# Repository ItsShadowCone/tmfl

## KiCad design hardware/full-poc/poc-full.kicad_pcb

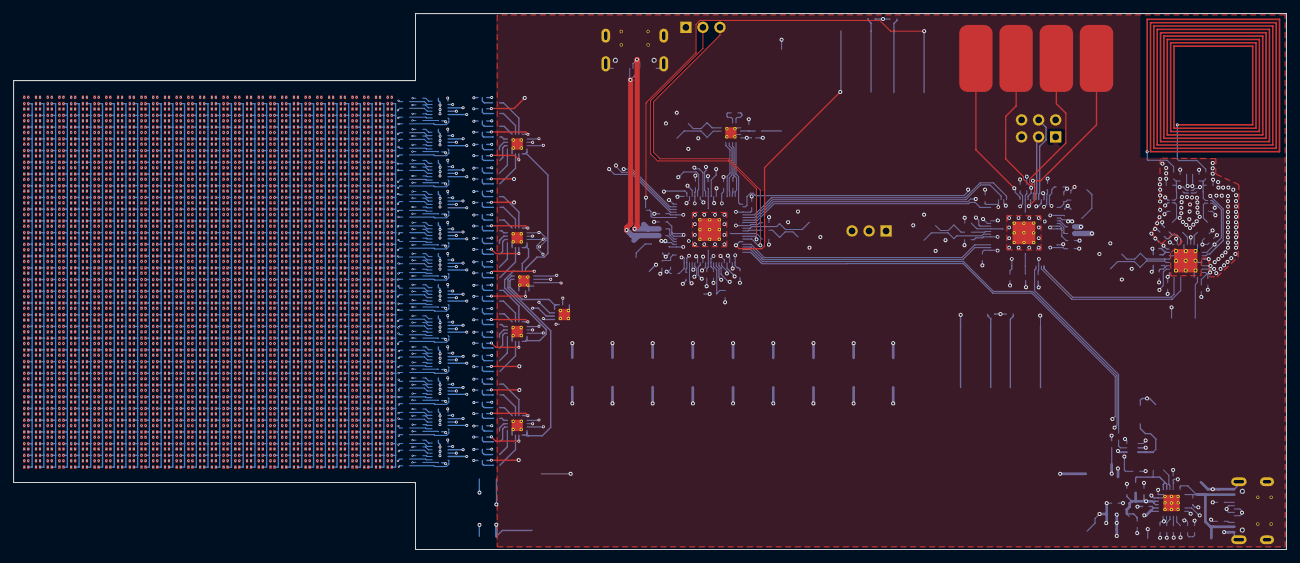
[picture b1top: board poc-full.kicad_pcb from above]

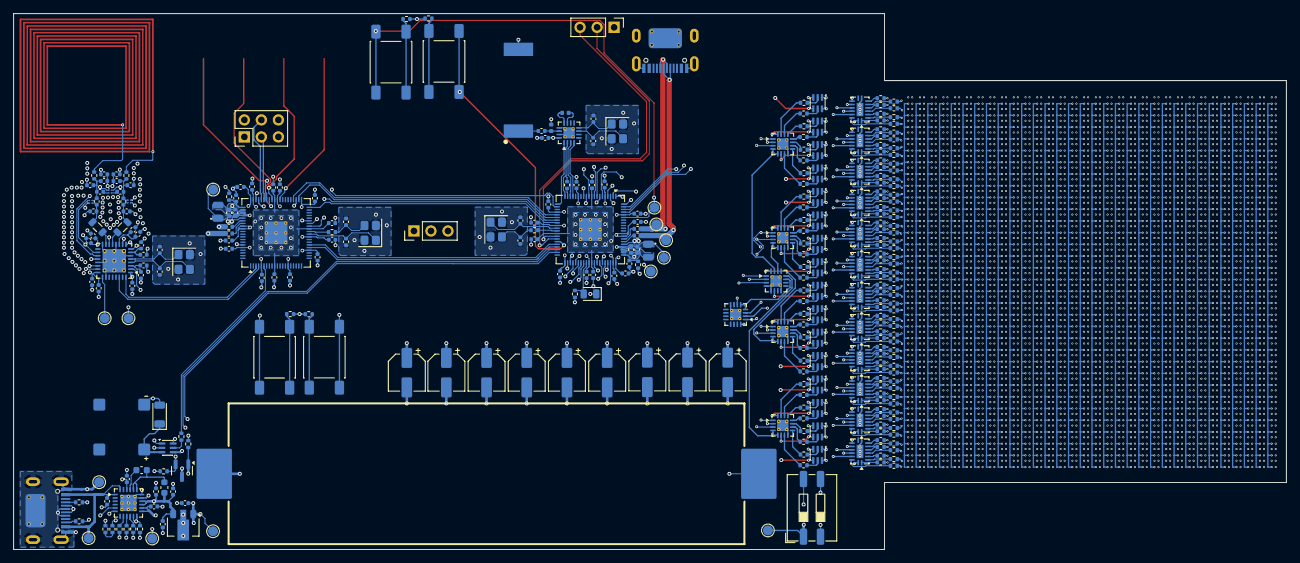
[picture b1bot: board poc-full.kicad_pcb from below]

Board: 4 copper layers, 190.0 x 80.0 mm, 1350 parts (321 on the bottom side), 422 nets.

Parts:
AE601: Antenna_Loop; NFC-Antenna
AE602: BW868MNX1304
BT301: Battery_Cell; BH-18650-B6AA002
BZ101: SMD7525-16Ω
C101, C103, C104, C105, C106, C107, C108, C109, C110, C111, C112, C113, C201, C203, C204, C205, C206, C207, C208, C209, C210, C211, C212, C213, C609, C628: 100n; C_0402_1005Metric
C102, C114, C115, C116, C202, C214, C215, C216, C305: 4.7u; C_0402_1005Metric
C117, C118, C217, C218, C610, C611: 15p; C_0402_1005Metric
C301, C306, C307, C613: 1u; C_0402_1005Metric
C302, C303, C308: 10u; C_0402_1005Metric
C304: 47n; C_0603_1608Metric
C401, C402, C403, C404, C405, C406, C407, C408, C409: 100u; CP_Elec_5x5.4
C601, C603, C605, C607: 2.2u; C_0402_1005Metric
C602, C604, C606, C608, C614: 10n; C_0402_1005Metric
C612: 100p; C_0402_1005Metric
C615, C619, C620, C624: 10p; C_0402_1005Metric
C616, C623: 22p; C_0402_1005Metric
C617, C621: 680p; C_0402_1005Metric
C618, C622, C625: 110p; C_0402_1005Metric
C626, C627: 25p; C_0402_1005Metric
C629: 2.7pF; C_0402_1005Metric
CAP101: CAP1; SolderWirePad_1x01_SMD_5x10mm
CAP102: CAP2; SolderWirePad_1x01_SMD_5x10mm
CAP103: CAP3; SolderWirePad_1x01_SMD_5x10mm
CAP104: CAP4; SolderWirePad_1x01_SMD_5x10mm
D1, D2, D3, D4, D5, D6, D7, D8, D9, D10, D11, D12, D13, D14, D15, D16, D17, D18, D19, D20, D21, D22, D23, D24, D25, D26, D27, D28, D29, D30, D31, D32, D33, D34, D35, D36, D37, D38, D39, D40, D41, D42, D43, D44, D45, D46, D47, D48, D49, D50, D51, D52, D53, D54, D55, D56, D57, D58, D59, D60, D61, D62, D63, D64, D65, D66, D67, D68, D69, D70, D71, D72, D73, D74, D75, D76, D77, D78, D79, D80, D81, D82, D83, D84, D85, D86, D87, D88, D89, D90, D91, D92, D93, D94, D95, D96, D97, D98, D99, D100, D101, D102, D103, D104, D105, D106, D107, D108, D109, D110, D111, D112, D113, D114, D115, D116, D117, D118, D119, D120, D121, D122, D123, D124, D125, D126, D127, D128, D129, D130, D131, D132, D133, D134, D135, D136, D137, D138, D139, D140, D141, D142, D143, D144, D145, D146, D147, D148, D149, D150, D151, D152, D153, D154, D155, D156, D157, D158, D159, D160, D161, D162, D163, D164, D165, D166, D167, D168, D169, D170, D171, D172, D173, D174, D175, D176, D177, D178, D179, D180, D181, D182, D183, D184, D185, D186, D187, D188, D189, D190, D191, D192, D193, D194, D195, D196, D197, D198, D199, D200, D201, D202, D203, D204, D205, D206, D207, D208, D209, D210, D211, D212, D213, D214, D215, D216, D217, D218, D219, D220, D221, D222, D223, D224, D225, D226, D227, D228, D229, D230, D231, D232, D233, D234, D235, D236, D237, D238, D239, D240, D241, D242, D243, D244, D245, D246, D247, D248, D249, D250, D251, D252, D253, D254, D255, D256, D257, D258, D259, D260, D261, D262, D263, D264, D265, D266, D267, D268, D269, D270, D271, D272, D273, D274, D275, D276, D277, D278, D279, D280, D281, D282, D283, D284, D285, D286, D287, D288, D289, D290, D291, D292, D293, D294, D295, D296, D297, D298, D299, D300, D301, D302, D303, D304, D305, D306, D307, D308, D309, D310, D311, D312, D313, D314, D315, D316, D317, D318, D319, D320, D321, D322, D323, D324, D325, D326, D327, D328, D329, D330, D331, D332, D333, D334, D335, D336, D337, D338, D339, D340, D341, D342, D343, D344, D345, D346, D347, D348, D349, D350, D351, D352, D353, D354, D355, D356, D357, D358, D359, D360, D361, D362, D363, D364, D365, D366, D367, D368, D369, D370, D371, D372, D373, D374, D375, D376, D377, D378, D379, D380, D381, D382, D383, D384, D385, D386, D387, D388, D389, D390, D391, D392, D393, D394, D395, D396, D397, D398, D399, D400, D401, D402, D403, D404, D405, D406, D407, D408, D409, D410, D411, D412, D413, D414, D415, D416, D417, D418, D419, D420, D421, D422, D423, D424, D425, D426, D427, D428, D429, D430, D431, D432, D433, D434, D435, D436, D437, D438, D439, D440, D441, D442, D443, D444, D445, D446, D447, D448, D449, D450, D451, D452, D453, D454, D455, D456, D457, D458, D459, D460, D461, D462, D463, D464, D465, D466, D467, D468, D469, D470, D471, D472, D473, D474, D475, D476, D477, D478, D479, D480, D481, D482, D483, D484, D485, D486, D487, D488, D489, D490, D491, D492, D493, D494, D495, D496, D497, D498, D499, D500, D501, D502, D503, D504, D505, D506, D507, D508, D509, D510, D511, D512, D513, D514, D515, D516, D517, D518, D519, D520, D521, D522, D523, D524, D525, D526, D527, D528, D529, D530, D531, D532, D533, D534, D535, D536, D537, D538, D539, D540, D541, D542, D543, D544, D545, D546, D547, D548, D549, D550, D551, D552, D553, D554, D555, D556, D557, D558, D559, D560, D561, D562, D563, D564, D565, D566, D567, D568, D569, D570, D571, D572, D573, D574, D575, D576, D577, D578, D579, D580, D581, D582, D583, D584, D585, D586, D587, D588, D589, D590, D591, D592, D593, D594, D595, D596, D597, D598, D599, D600, D601, D602, D603, D604, D605, D606, D607, D608, D609, D610, D611, D612, D613, D614, D615, D616, D617, D618, D619, D620, D621, D622, D623, D624, D625, D626, D627, D628, D629, D630, D631, D632, D633, D634, D635, D636, D637, D638, D639, D640, D641, D642, D643, D644, D645, D646, D647, D648, D649, D650, D651, D652, D653, D654, D655, D656, D657, D658, D659, D660, D661, D662, D663, D664, D665, D666, D667, D668, D669, D670, D671, D672, D673, D674, D675, D676, D677, D678, D679, D680, D681, D682, D683, D684, D685, D686, D687, D688, D689, D690, D691, D692, D693, D694, D695, D696, D697, D698, D699, D700, D701, D702, D703, D704, D705, D706, D707, D708, D709, D710, D711, D712, D713, D714, D715, D716, D717, D718, D719, D720, D721, D722, D723, D724, D725, D726, D727, D728, D729, D730, D731, D732, D733, D734, D735, D736, D737, D738, D739, D740, D741, D742, D743, D744, D745, D746, D747, D748, D749, D750, D751, D752, D753, D754, D755, D756, D757, D758, D759, D760, D761, D762, D763, D764, D765, D766, D767, D768, D769, D770, D771, D772, D773, D774, D775, D776, D777, D778, D779, D780, D781, D782, D783, D784, D785, D786, D787, D788, D789, D790, D791, D792, D793, D794, D795, D796, D797, D798, D799, D800, D801, D802, D803, D804, D805, D806, D807, D808, D809, D810, D811, D812, D813, D814, D815, D816, D817, D818, D819, D820, D821, D822, D823, D824, D825, D826, D827, D828, D829, D830, D831, D832, D833, D834, D835, D836, D837, D838, D839, D840, D841, D842, D843, D844, D845, D846, D847, D848, D849, D850, D851, D852, D853, D854, D855, D856, D857, D858, D859, D860, D861, D862, D863, D864, D865, D866, D867, D868, D869, D870, D871, D872, D873, D874, D875, D876, D877, D878, D879, D880, D881, D882, D883, D884, D885, D886, D887, D888, D889, D890, D891, D892, D893, D894, D895, D896, D897, D898, D899, D900, D901, D902, D903, D904, D905, D906, D907, D908, D909, D910, D911, D912, D913, D914, D915, D916, D917, D918, D919, D920, D921, D922, D923, D924, D925, D926, D927, D928, D929, D930, D931, D932, D933, D934, D935, D936, D937, D938, D939, D940, D941, D942, D943, D944, D945, D946, D947, D948, D949, D950, D951, D952, D953, D954, D955, D956, D957, D958, D959, D960, D961, D962, D963, D964, D965, D966, D967, D968, D969, D970, D971, D972, D973, D974, D975, D976, D977, D978, D979, D980, D981, D982, D983, D984, D985, D986, D987, D988, D989, D990, D991, D992, D993, D994, D995, D996, D997, D998, D999, D1000, D1001, D1002, D1003, D1004, D1005, D1006, D1007, D1008, D1009, D1010, D1011, D1012, D1013, D1014, D1015, D1016, D1017, D1018, D1019, D1020, D1021, D1022, D1023, D1024: LED_RABG; NH-B1212RGBA-HF
D1281: SM4007PL; D_SOD-123FL
J101, J201: DEBUG; PinHeader_1x03_P2.54mm_Vertical
J102: SAO V1.69bis; PinHeader_2x03_P2.54mm_Vertical
J202, J301: Connector, USB-TYPE-C-16P; TYPE-C-SMD_HX-TYPE-C-16PIN
L101, L201: 3.3u; AOTA-B201610S3R3-101-T
L301: 2u2; L_0603_1608Metric
L601, L602: 270nH, 500mΩ; L_0805_2012Metric
L603: 3.9nH; L_0402_1005Metric
L604: 6.8nH; L_0402_1005Metric
Q201: XYC-PT0805BC-L4-D; D_0805
Q301, Q401, Q402, Q403, Q404, Q405, Q406, Q407, Q408, Q409, Q410, Q411, Q412, Q413, Q414, Q415, Q416: BC857BS; SOT-363_SC-70-6
Q302: SI2302; Q_SOT-23
R101, R201: 33; R_0402_1005Metric
R102, R103, R202, R203: 27; R_0402_1005Metric
R104, R105, R106, R107, R204, R206, R207, R497, R498, R499, R500, R501, R502, R503, R504, R505, R506, R507, R508, R509, R510, R511, R512, R513, R514, R515, R516, R517, R518, R519, R520, R521, R522, R523, R524, R525, R526, R527, R528: 1k; R_0402_1005Metric
R205, R208, R303, R307, R308, R309, R310: 10k; R_0402_1005Metric
R301, R302, R304: 5.1k; R_0402_1005Metric
R305: 220; R_0402_1005Metric
R306: 1.5k; R_0402_1005Metric
R401, R404, R407, R410, R413, R416, R419, R422, R425, R428, R431, R434, R437, R440, R443, R446, R449, R452, R455, R458, R461, R464, R467, R470, R473, R476, R479, R482, R485, R488, R491, R494: 130; R_0402_1005Metric
R402, R405, R408, R411, R414, R417, R420, R423, R426, R429, R432, R435, R438, R441, R444, R447, R450, R453, R456, R459, R462, R465, R468, R471, R474, R477, R480, R483, R486, R489, R492, R495: 360; R_0402_1005Metric
R403, R406, R409, R412, R415, R418, R421, R424, R427, R430, R433, R436, R439, R442, R445, R448, R451, R454, R457, R460, R463, R466, R469, R472, R475, R478, R481, R484, R487, R490, R493, R496: 82; R_0402_1005Metric
R601, R602: 3; R_0402_1005Metric
SW101, SW102, SW201, SW202: KH-6X6X5H-STM; SW_Push_1P1T_NO_E-Switch_TL3301NxxxxxG
SW301: BAT_SOFT_OFF HY-DSIC02LS; SW_DIP_SPSTx02_Slide_9.78x7.26mm_W8.61mm_P2.54mm
TP101, TP201: +1V1; TestPoint_Pad_D1.5mm
TP202: DPU_USB_D+; TestPoint_Pad_D1.5mm
TP203: DPU_USB_D-; TestPoint_Pad_D1.5mm
TP204: DPU_BOOTSEL; TestPoint_Pad_D1.5mm
TP205: DPU_RUN; TestPoint_Pad_D1.5mm
TP301: VBAT; TestPoint_Pad_D1.5mm
TP302: VBUS; TestPoint_Pad_D1.5mm
TP303: GND; TestPoint_Pad_D1.5mm
TP304: +3V8 / VSYS; TestPoint_Pad_D1.5mm
TP305: +3V3; TestPoint_Pad_D1.5mm
TP601: NFC_TP1; TestPoint_Pad_D1.5mm
TP602: NFC_TP2; TestPoint_Pad_D1.5mm
U101, U201: RP2354_80QFN; QFN-80-1EP_10x10mm_P0.4mm_EP3.4x3.4mm_ThermalVias
U301: BQ24195LRGER; VQFN-24-1EP_4x4mm_P0.5mm_EP2.45x2.45mm_ThermalVias
U302: H7650-33PR; SOT-89-3
U401, U402, U403, U404, U405, U406, U407, U408, U409, U410, U411, U412: 74HC595BQ; DHVQFN-16-1EP_2.5x3.5mm_P0.5mm_EP1x2mm
U413, U414, U415, U416, U417, U418: 74HC138LQ/TR; QFN-16-1EP_3x3mm_P0.5mm_EP1.7x1.7mm_ThermalVias
U601: ST25R3916B-AQWT; VQFN-32-1EP_5x5mm_P0.5mm_EP3.5x3.5mm_ThermalVias
U602: CMT2219A; QFN-16-1EP_3x3mm_P0.5mm_EP1.7x1.7mm_ThermalVias
VCC601, VCC602, VCC603: LXRW0YV600-054
Y101, Y201: ABM8-272-T3; Crystal_SMD_3225-4Pin_3.2x2.5mm
Y601: 5YMA27120091KF50EB; Crystal_SMD_3225-4Pin_3.2x2.5mm
Y602: TAXM26M4RHBCCT2T; Crystal_SMD_3225-4Pin_3.2x2.5mm

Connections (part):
+3V3: C104.1, C105.1, C106.1, C107.1, C108.1, C109.1, C110.1, C111.1, C112.1, C113.2, C115.1, C204.1, C205.1, C206.1, C207.1, C208.1, C209.1, C210.1, C211.1, C212.1, C213.2, C215.1, C307.1, C401.1, C402.1, C403.1, C404.1, C405.1, C406.1, C407.1, C408.1, C409.1, C609.1, C628.1, J102.1, Q201.1 (C), Q301.4 (E2), Q401.1 (E1), Q401.4 (E2), Q402.1 (E1), Q402.4 (E2), Q403.1 (E1), Q403.4 (E2), Q404.1 (E1), Q404.4 (E2), Q405.1 (E1), Q405.4 (E2), Q406.1 (E1), Q406.4 (E2), Q407.1 (E1), Q407.4 (E2), Q408.1 (E1), Q408.4 (E2), Q409.1 (E1), Q409.4 (E2), Q410.1 (E1), Q410.4 (E2), Q411.1 (E1), Q411.4 (E2), Q412.1 (E1), Q412.4 (E2), Q413.1 (E1), Q413.4 (E2), Q414.1 (E1), Q414.4 (E2), Q415.1 (E1), Q415.4 (E2), Q416.1 (E1), Q416.4 (E2), R101.1, R201.1, TP305.1 (1_1), U101.5 (IOVDD), U101.15 (IOVDD), U101.24 (IOVDD), U101.29 (IOVDD), U101.41 (IOVDD), U101.50 (IOVDD), U101.59 (ADC_AVDD), U101.60 (IOVDD), U101.64 (VREG_VIN), U101.68 (USB_OTP_VDD), U101.69 (QSPI_IOVDD), U101.76 (IOVDD), U201.5 (IOVDD), U201.15 (IOVDD), U201.24 (IOVDD)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
+3V8: C302.2, C303.2, C306.1, L301.2, R303.1, TP304.1 (1_1), U301.15 (SYS), U301.16 (SYS), U302.3 (VI)
/Battery/SCL: U201.39 (GPIO31), U301.5 (SCL)
/Battery/SDA: U201.38 (GPIO30), U301.6 (SDA)
/Battery/SOFT-OFF: SW301.2, U201.42 (GPIO33)
/Battery/USB_D+: J301.A6 (D+), J301.B6 (D+), R102.1
/Battery/USB_D-: J301.A7 (D-), J301.B7 (D-), R103.1
/Display_Unit/D-CIPO: U101.40 (GPIO32), U201.28 (GPIO27)
/Display_Unit/D-COPI: U101.44 (GPIO35), U201.25 (GPIO24)
/Display_Unit/D-CS: U101.42 (GPIO33), U201.26 (GPIO25)
/Display_Unit/D-RX: U101.25 (GPIO24), U201.37 (GPIO29)
/Display_Unit/D-SCK: U101.43 (GPIO34), U201.27 (GPIO26)
/Display_Unit/D-TX: U101.26 (GPIO25), U201.36 (GPIO28)
/Display_Unit/DISP-CLK: U201.78 (GPIO1), U401.11 (SRCLK), U402.11 (SRCLK), U403.11 (SRCLK), U404.11 (SRCLK), U405.11 (SRCLK), U406.11 (SRCLK), U407.11 (SRCLK), U408.11 (SRCLK), U409.11 (SRCLK), U410.11 (SRCLK), U411.11 (SRCLK), U412.11 (SRCLK)
/Display_Unit/DISP-C_P_1: U201.43 (GPIO34), U413.1 (A0), U415.1 (A0), U416.1 (A0), U417.1 (A0), U418.3 (A2)
/Display_Unit/DISP-C_P_2: U201.44 (GPIO35), U413.2 (A1), U415.2 (A1), U416.2 (A1), U417.2 (A1), U418.2 (A1)
/Display_Unit/DISP-C_P_3: U201.45 (GPIO36), U413.3 (A2), U415.3 (A2), U416.3 (A2), U417.3 (A2), U418.1 (A0)
/Display_Unit/DISP-C_P_4: U201.46 (GPIO37), U414.1 (A0)
/Display_Unit/DISP-C_P_5: U201.47 (GPIO38), U414.2 (A1)
/Display_Unit/DISP-C_P_6: U201.48 (GPIO39), U414.3 (A2)
/Display_Unit/DISP-R_S_1: U201.80 (GPIO3), U401.14 (SER)
/Display_Unit/DISP-R_S_2: U201.1 (GPIO4), U402.14 (SER)
/Display_Unit/DISP-R_S_3: U201.2 (GPIO5), U403.14 (SER)
/Display_Unit/DISP-R_S_4: U201.3 (GPIO6), U404.14 (SER)
/Display_Unit/DISP-R_S_5: U201.4 (GPIO7), U405.14 (SER)
/Display_Unit/DISP-R_S_6: U201.6 (GPIO8), U406.14 (SER)
/Display_Unit/DISP-R_S_7: U201.7 (GPIO9), U407.14 (SER)
/Display_Unit/DISP-R_S_8: U201.8 (GPIO10), U408.14 (SER)
/Display_Unit/DISP-R_S_9: U201.9 (GPIO11), U409.14 (SER)
/Display_Unit/DISP-R_S_10: U201.11 (GPIO12), U410.14 (SER)
/Display_Unit/DISP-R_S_11: U201.12 (GPIO13), U411.14 (SER)
/Display_Unit/DISP-R_S_12: U201.13 (GPIO14), U412.14 (SER)
/Display_Unit/DISP-STOP: U201.77 (GPIO0), U401.12 (RCLK), U402.12 (RCLK), U403.12 (RCLK), U404.12 (RCLK), U405.12 (RCLK), U406.12 (RCLK), U407.12 (RCLK), U408.12 (RCLK), U409.12 (RCLK), U410.12 (RCLK), U411.12 (RCLK), U412.12 (RCLK)
/Display_Unit/DISP-~OE: U201.79 (GPIO2), U401.13 (~OE), U402.13 (~OE), U403.13 (~OE), U404.13 (~OE), U405.13 (~OE), U406.13 (~OE), U407.13 (~OE), U408.13 (~OE), U409.13 (~OE), U410.13 (~OE), U411.13 (~OE), U412.13 (~OE)
/Display_Unit/SUBG-CS: U201.21 (GPIO21), U602.1 (CSB)
/Display_Unit/SUBG-FCS: U201.17 (GPIO17), U602.4 (FCSB)
/Display_Unit/SUBG-SCK: U201.18 (GPIO18), U602.3 (SCL)
/Display_Unit/SUBG-SDA: R205.2, U201.20 (GPIO20), U602.2 (SDA)
/LED_control/LED_matrix/+0: D1.2 (A), D33.2 (A), D65.2 (A), D97.2 (A), D129.2 (A), D161.2 (A), D193.2 (A), D225.2 (A), D257.2 (A), D289.2 (A), D321.2 (A), D353.2 (A), D385.2 (A), D417.2 (A), D449.2 (A), D481.2 (A), D513.2 (A), D545.2 (A), D577.2 (A), D609.2 (A), D641.2 (A), D673.2 (A), D705.2 (A), D737.2 (A), D769.2 (A), D801.2 (A), D833.2 (A), D865.2 (A), D897.2 (A), D929.2 (A), D961.2 (A), D993.2 (A), Q401.6 (C1)
/LED_control/LED_matrix/+1: D2.2 (A), D34.2 (A), D66.2 (A), D98.2 (A), D130.2 (A), D162.2 (A), D194.2 (A), D226.2 (A), D258.2 (A), D290.2 (A), D322.2 (A), D354.2 (A), D386.2 (A), D418.2 (A), D450.2 (A), D482.2 (A), D514.2 (A), D546.2 (A), D578.2 (A), D610.2 (A), D642.2 (A), D674.2 (A), D706.2 (A), D738.2 (A), D770.2 (A), D802.2 (A), D834.2 (A), D866.2 (A), D898.2 (A), D930.2 (A), D962.2 (A), D994.2 (A), Q401.3 (C2)
/LED_control/LED_matrix/+2: D3.2 (A), D35.2 (A), D67.2 (A), D99.2 (A), D131.2 (A), D163.2 (A), D195.2 (A), D227.2 (A), D259.2 (A), D291.2 (A), D323.2 (A), D355.2 (A), D387.2 (A), D419.2 (A), D451.2 (A), D483.2 (A), D515.2 (A), D547.2 (A), D579.2 (A), D611.2 (A), D643.2 (A), D675.2 (A), D707.2 (A), D739.2 (A), D771.2 (A), D803.2 (A), D835.2 (A), D867.2 (A), D899.2 (A), D931.2 (A), D963.2 (A), D995.2 (A), Q402.6 (C1)
/LED_control/LED_matrix/+3: D4.2 (A), D36.2 (A), D68.2 (A), D100.2 (A), D132.2 (A), D164.2 (A), D196.2 (A), D228.2 (A), D260.2 (A), D292.2 (A), D324.2 (A), D356.2 (A), D388.2 (A), D420.2 (A), D452.2 (A), D484.2 (A), D516.2 (A), D548.2 (A), D580.2 (A), D612.2 (A), D644.2 (A), D676.2 (A), D708.2 (A), D740.2 (A), D772.2 (A), D804.2 (A), D836.2 (A), D868.2 (A), D900.2 (A), D932.2 (A), D964.2 (A), D996.2 (A), Q402.3 (C2)
/LED_control/LED_matrix/+4: D5.2 (A), D37.2 (A), D69.2 (A), D101.2 (A), D133.2 (A), D165.2 (A), D197.2 (A), D229.2 (A), D261.2 (A), D293.2 (A), D325.2 (A), D357.2 (A), D389.2 (A), D421.2 (A), D453.2 (A), D485.2 (A), D517.2 (A), D549.2 (A), D581.2 (A), D613.2 (A), D645.2 (A), D677.2 (A), D709.2 (A), D741.2 (A), D773.2 (A), D805.2 (A), D837.2 (A), D869.2 (A), D901.2 (A), D933.2 (A), D965.2 (A), D997.2 (A), Q403.6 (C1)
/LED_control/LED_matrix/+5: D6.2 (A), D38.2 (A), D70.2 (A), D102.2 (A), D134.2 (A), D166.2 (A), D198.2 (A), D230.2 (A), D262.2 (A), D294.2 (A), D326.2 (A), D358.2 (A), D390.2 (A), D422.2 (A), D454.2 (A), D486.2 (A), D518.2 (A), D550.2 (A), D582.2 (A), D614.2 (A), D646.2 (A), D678.2 (A), D710.2 (A), D742.2 (A), D774.2 (A), D806.2 (A), D838.2 (A), D870.2 (A), D902.2 (A), D934.2 (A), D966.2 (A), D998.2 (A), Q403.3 (C2)
/LED_control/LED_matrix/+6: D7.2 (A), D39.2 (A), D71.2 (A), D103.2 (A), D135.2 (A), D167.2 (A), D199.2 (A), D231.2 (A), D263.2 (A), D295.2 (A), D327.2 (A), D359.2 (A), D391.2 (A), D423.2 (A), D455.2 (A), D487.2 (A), D519.2 (A), D551.2 (A), D583.2 (A), D615.2 (A), D647.2 (A), D679.2 (A), D711.2 (A), D743.2 (A), D775.2 (A), D807.2 (A), D839.2 (A), D871.2 (A), D903.2 (A), D935.2 (A), D967.2 (A), D999.2 (A), Q404.6 (C1)
/LED_control/LED_matrix/+7: D8.2 (A), D40.2 (A), D72.2 (A), D104.2 (A), D136.2 (A), D168.2 (A), D200.2 (A), D232.2 (A), D264.2 (A), D296.2 (A), D328.2 (A), D360.2 (A), D392.2 (A), D424.2 (A), D456.2 (A), D488.2 (A), D520.2 (A), D552.2 (A), D584.2 (A), D616.2 (A), D648.2 (A), D680.2 (A), D712.2 (A), D744.2 (A), D776.2 (A), D808.2 (A), D840.2 (A), D872.2 (A), D904.2 (A), D936.2 (A), D968.2 (A), D1000.2 (A), Q404.3 (C2)
/LED_control/LED_matrix/+8: D9.2 (A), D41.2 (A), D73.2 (A), D105.2 (A), D137.2 (A), D169.2 (A), D201.2 (A), D233.2 (A), D265.2 (A), D297.2 (A), D329.2 (A), D361.2 (A), D393.2 (A), D425.2 (A), D457.2 (A), D489.2 (A), D521.2 (A), D553.2 (A), D585.2 (A), D617.2 (A), D649.2 (A), D681.2 (A), D713.2 (A), D745.2 (A), D777.2 (A), D809.2 (A), D841.2 (A), D873.2 (A), D905.2 (A), D937.2 (A), D969.2 (A), D1001.2 (A), Q405.6 (C1)
/LED_control/LED_matrix/+9: D10.2 (A), D42.2 (A), D74.2 (A), D106.2 (A), D138.2 (A), D170.2 (A), D202.2 (A), D234.2 (A), D266.2 (A), D298.2 (A), D330.2 (A), D362.2 (A), D394.2 (A), D426.2 (A), D458.2 (A), D490.2 (A), D522.2 (A), D554.2 (A), D586.2 (A), D618.2 (A), D650.2 (A), D682.2 (A), D714.2 (A), D746.2 (A), D778.2 (A), D810.2 (A), D842.2 (A), D874.2 (A), D906.2 (A), D938.2 (A), D970.2 (A), D1002.2 (A), Q405.3 (C2)
/LED_control/LED_matrix/+10: D11.2 (A), D43.2 (A), D75.2 (A), D107.2 (A), D139.2 (A), D171.2 (A), D203.2 (A), D235.2 (A), D267.2 (A), D299.2 (A), D331.2 (A), D363.2 (A), D395.2 (A), D427.2 (A), D459.2 (A), D491.2 (A), D523.2 (A), D555.2 (A), D587.2 (A), D619.2 (A), D651.2 (A), D683.2 (A), D715.2 (A), D747.2 (A), D779.2 (A), D811.2 (A), D843.2 (A), D875.2 (A), D907.2 (A), D939.2 (A), D971.2 (A), D1003.2 (A), Q406.6 (C1)
/LED_control/LED_matrix/+11: D12.2 (A), D44.2 (A), D76.2 (A), D108.2 (A), D140.2 (A), D172.2 (A), D204.2 (A), D236.2 (A), D268.2 (A), D300.2 (A), D332.2 (A), D364.2 (A), D396.2 (A), D428.2 (A), D460.2 (A), D492.2 (A), D524.2 (A), D556.2 (A), D588.2 (A), D620.2 (A), D652.2 (A), D684.2 (A), D716.2 (A), D748.2 (A), D780.2 (A), D812.2 (A), D844.2 (A), D876.2 (A), D908.2 (A), D940.2 (A), D972.2 (A), D1004.2 (A), Q406.3 (C2)
/LED_control/LED_matrix/+12: D13.2 (A), D45.2 (A), D77.2 (A), D109.2 (A), D141.2 (A), D173.2 (A), D205.2 (A), D237.2 (A), D269.2 (A), D301.2 (A), D333.2 (A), D365.2 (A), D397.2 (A), D429.2 (A), D461.2 (A), D493.2 (A), D525.2 (A), D557.2 (A), D589.2 (A), D621.2 (A), D653.2 (A), D685.2 (A), D717.2 (A), D749.2 (A), D781.2 (A), D813.2 (A), D845.2 (A), D877.2 (A), D909.2 (A), D941.2 (A), D973.2 (A), D1005.2 (A), Q407.6 (C1)
/LED_control/LED_matrix/+13: D14.2 (A), D46.2 (A), D78.2 (A), D110.2 (A), D142.2 (A), D174.2 (A), D206.2 (A), D238.2 (A), D270.2 (A), D302.2 (A), D334.2 (A), D366.2 (A), D398.2 (A), D430.2 (A), D462.2 (A), D494.2 (A), D526.2 (A), D558.2 (A), D590.2 (A), D622.2 (A), D654.2 (A), D686.2 (A), D718.2 (A), D750.2 (A), D782.2 (A), D814.2 (A), D846.2 (A), D878.2 (A), D910.2 (A), D942.2 (A), D974.2 (A), D1006.2 (A), Q407.3 (C2)
/LED_control/LED_matrix/+14: D15.2 (A), D47.2 (A), D79.2 (A), D111.2 (A), D143.2 (A), D175.2 (A), D207.2 (A), D239.2 (A), D271.2 (A), D303.2 (A), D335.2 (A), D367.2 (A), D399.2 (A), D431.2 (A), D463.2 (A), D495.2 (A), D527.2 (A), D559.2 (A), D591.2 (A), D623.2 (A), D655.2 (A), D687.2 (A), D719.2 (A), D751.2 (A), D783.2 (A), D815.2 (A), D847.2 (A), D879.2 (A), D911.2 (A), D943.2 (A), D975.2 (A), D1007.2 (A), Q408.6 (C1)
/LED_control/LED_matrix/+15: D16.2 (A), D48.2 (A), D80.2 (A), D112.2 (A), D144.2 (A), D176.2 (A), D208.2 (A), D240.2 (A), D272.2 (A), D304.2 (A), D336.2 (A), D368.2 (A), D400.2 (A), D432.2 (A), D464.2 (A), D496.2 (A), D528.2 (A), D560.2 (A), D592.2 (A), D624.2 (A), D656.2 (A), D688.2 (A), D720.2 (A), D752.2 (A), D784.2 (A), D816.2 (A), D848.2 (A), D880.2 (A), D912.2 (A), D944.2 (A), D976.2 (A), D1008.2 (A), Q408.3 (C2)
/LED_control/LED_matrix/+16: D17.2 (A), D49.2 (A), D81.2 (A), D113.2 (A), D145.2 (A), D177.2 (A), D209.2 (A), D241.2 (A), D273.2 (A), D305.2 (A), D337.2 (A), D369.2 (A), D401.2 (A), D433.2 (A), D465.2 (A), D497.2 (A), D529.2 (A), D561.2 (A), D593.2 (A), D625.2 (A), D657.2 (A), D689.2 (A), D721.2 (A), D753.2 (A), D785.2 (A), D817.2 (A), D849.2 (A), D881.2 (A), D913.2 (A), D945.2 (A), D977.2 (A), D1009.2 (A), Q409.6 (C1)
/LED_control/LED_matrix/+17: D18.2 (A), D50.2 (A), D82.2 (A), D114.2 (A), D146.2 (A), D178.2 (A), D210.2 (A), D242.2 (A), D274.2 (A), D306.2 (A), D338.2 (A), D370.2 (A), D402.2 (A), D434.2 (A), D466.2 (A), D498.2 (A), D530.2 (A), D562.2 (A), D594.2 (A), D626.2 (A), D658.2 (A), D690.2 (A), D722.2 (A), D754.2 (A), D786.2 (A), D818.2 (A), D850.2 (A), D882.2 (A), D914.2 (A), D946.2 (A), D978.2 (A), D1010.2 (A), Q409.3 (C2)
/LED_control/LED_matrix/+18: D19.2 (A), D51.2 (A), D83.2 (A), D115.2 (A), D147.2 (A), D179.2 (A), D211.2 (A), D243.2 (A), D275.2 (A), D307.2 (A), D339.2 (A), D371.2 (A), D403.2 (A), D435.2 (A), D467.2 (A), D499.2 (A), D531.2 (A), D563.2 (A), D595.2 (A), D627.2 (A), D659.2 (A), D691.2 (A), D723.2 (A), D755.2 (A), D787.2 (A), D819.2 (A), D851.2 (A), D883.2 (A), D915.2 (A), D947.2 (A), D979.2 (A), D1011.2 (A), Q410.6 (C1)
/LED_control/LED_matrix/+19: D20.2 (A), D52.2 (A), D84.2 (A), D116.2 (A), D148.2 (A), D180.2 (A), D212.2 (A), D244.2 (A), D276.2 (A), D308.2 (A), D340.2 (A), D372.2 (A), D404.2 (A), D436.2 (A), D468.2 (A), D500.2 (A), D532.2 (A), D564.2 (A), D596.2 (A), D628.2 (A), D660.2 (A), D692.2 (A), D724.2 (A), D756.2 (A), D788.2 (A), D820.2 (A), D852.2 (A), D884.2 (A), D916.2 (A), D948.2 (A), D980.2 (A), D1012.2 (A), Q410.3 (C2)
/LED_control/LED_matrix/+20: D21.2 (A), D53.2 (A), D85.2 (A), D117.2 (A), D149.2 (A), D181.2 (A), D213.2 (A), D245.2 (A), D277.2 (A), D309.2 (A), D341.2 (A), D373.2 (A), D405.2 (A), D437.2 (A), D469.2 (A), D501.2 (A), D533.2 (A), D565.2 (A), D597.2 (A), D629.2 (A), D661.2 (A), D693.2 (A), D725.2 (A), D757.2 (A), D789.2 (A), D821.2 (A), D853.2 (A), D885.2 (A), D917.2 (A), D949.2 (A), D981.2 (A), D1013.2 (A), Q411.6 (C1)
/LED_control/LED_matrix/+21: D22.2 (A), D54.2 (A), D86.2 (A), D118.2 (A), D150.2 (A), D182.2 (A), D214.2 (A), D246.2 (A), D278.2 (A), D310.2 (A), D342.2 (A), D374.2 (A), D406.2 (A), D438.2 (A), D470.2 (A), D502.2 (A), D534.2 (A), D566.2 (A), D598.2 (A), D630.2 (A), D662.2 (A), D694.2 (A), D726.2 (A), D758.2 (A), D790.2 (A), D822.2 (A), D854.2 (A), D886.2 (A), D918.2 (A), D950.2 (A), D982.2 (A), D1014.2 (A), Q411.3 (C2)
/LED_control/LED_matrix/+22: D23.2 (A), D55.2 (A), D87.2 (A), D119.2 (A), D151.2 (A), D183.2 (A), D215.2 (A), D247.2 (A), D279.2 (A), D311.2 (A), D343.2 (A), D375.2 (A), D407.2 (A), D439.2 (A), D471.2 (A), D503.2 (A), D535.2 (A), D567.2 (A), D599.2 (A), D631.2 (A), D663.2 (A), D695.2 (A), D727.2 (A), D759.2 (A), D791.2 (A), D823.2 (A), D855.2 (A), D887.2 (A), D919.2 (A), D951.2 (A), D983.2 (A), D1015.2 (A), Q412.6 (C1)
/LED_control/LED_matrix/+23: D24.2 (A), D56.2 (A), D88.2 (A), D120.2 (A), D152.2 (A), D184.2 (A), D216.2 (A), D248.2 (A), D280.2 (A), D312.2 (A), D344.2 (A), D376.2 (A), D408.2 (A), D440.2 (A), D472.2 (A), D504.2 (A), D536.2 (A), D568.2 (A), D600.2 (A), D632.2 (A), D664.2 (A), D696.2 (A), D728.2 (A), D760.2 (A), D792.2 (A), D824.2 (A), D856.2 (A), D888.2 (A), D920.2 (A), D952.2 (A), D984.2 (A), D1016.2 (A), Q412.3 (C2)
/LED_control/LED_matrix/+24: D25.2 (A), D57.2 (A), D89.2 (A), D121.2 (A), D153.2 (A), D185.2 (A), D217.2 (A), D249.2 (A), D281.2 (A), D313.2 (A), D345.2 (A), D377.2 (A), D409.2 (A), D441.2 (A), D473.2 (A), D505.2 (A), D537.2 (A), D569.2 (A), D601.2 (A), D633.2 (A), D665.2 (A), D697.2 (A), D729.2 (A), D761.2 (A), D793.2 (A), D825.2 (A), D857.2 (A), D889.2 (A), D921.2 (A), D953.2 (A), D985.2 (A), D1017.2 (A), Q413.6 (C1)
/LED_control/LED_matrix/+25: D26.2 (A), D58.2 (A), D90.2 (A), D122.2 (A), D154.2 (A), D186.2 (A), D218.2 (A), D250.2 (A), D282.2 (A), D314.2 (A), D346.2 (A), D378.2 (A), D410.2 (A), D442.2 (A), D474.2 (A), D506.2 (A), D538.2 (A), D570.2 (A), D602.2 (A), D634.2 (A), D666.2 (A), D698.2 (A), D730.2 (A), D762.2 (A), D794.2 (A), D826.2 (A), D858.2 (A), D890.2 (A), D922.2 (A), D954.2 (A), D986.2 (A), D1018.2 (A), Q413.3 (C2)
/LED_control/LED_matrix/+26: D27.2 (A), D59.2 (A), D91.2 (A), D123.2 (A), D155.2 (A), D187.2 (A), D219.2 (A), D251.2 (A), D283.2 (A), D315.2 (A), D347.2 (A), D379.2 (A), D411.2 (A), D443.2 (A), D475.2 (A), D507.2 (A), D539.2 (A), D571.2 (A), D603.2 (A), D635.2 (A), D667.2 (A), D699.2 (A), D731.2 (A), D763.2 (A), D795.2 (A), D827.2 (A), D859.2 (A), D891.2 (A), D923.2 (A), D955.2 (A), D987.2 (A), D1019.2 (A), Q414.6 (C1)
/LED_control/LED_matrix/+27: D28.2 (A), D60.2 (A), D92.2 (A), D124.2 (A), D156.2 (A), D188.2 (A), D220.2 (A), D252.2 (A), D284.2 (A), D316.2 (A), D348.2 (A), D380.2 (A), D412.2 (A), D444.2 (A), D476.2 (A), D508.2 (A), D540.2 (A), D572.2 (A), D604.2 (A), D636.2 (A), D668.2 (A), D700.2 (A), D732.2 (A), D764.2 (A), D796.2 (A), D828.2 (A), D860.2 (A), D892.2 (A), D924.2 (A), D956.2 (A), D988.2 (A), D1020.2 (A), Q414.3 (C2)
/LED_control/LED_matrix/+28: D29.2 (A), D61.2 (A), D93.2 (A), D125.2 (A), D157.2 (A), D189.2 (A), D221.2 (A), D253.2 (A), D285.2 (A), D317.2 (A), D349.2 (A), D381.2 (A), D413.2 (A), D445.2 (A), D477.2 (A), D509.2 (A), D541.2 (A), D573.2 (A), D605.2 (A), D637.2 (A), D669.2 (A), D701.2 (A), D733.2 (A), D765.2 (A), D797.2 (A), D829.2 (A), D861.2 (A), D893.2 (A), D925.2 (A), D957.2 (A), D989.2 (A), D1021.2 (A), Q415.6 (C1)
/LED_control/LED_matrix/+29: D30.2 (A), D62.2 (A), D94.2 (A), D126.2 (A), D158.2 (A), D190.2 (A), D222.2 (A), D254.2 (A), D286.2 (A), D318.2 (A), D350.2 (A), D382.2 (A), D414.2 (A), D446.2 (A), D478.2 (A), D510.2 (A), D542.2 (A), D574.2 (A), D606.2 (A), D638.2 (A), D670.2 (A), D702.2 (A), D734.2 (A), D766.2 (A), D798.2 (A), D830.2 (A), D862.2 (A), D894.2 (A), D926.2 (A), D958.2 (A), D990.2 (A), D1022.2 (A), Q415.3 (C2)
/LED_control/LED_matrix/+30: D31.2 (A), D63.2 (A), D95.2 (A), D127.2 (A), D159.2 (A), D191.2 (A), D223.2 (A), D255.2 (A), D287.2 (A), D319.2 (A), D351.2 (A), D383.2 (A), D415.2 (A), D447.2 (A), D479.2 (A), D511.2 (A), D543.2 (A), D575.2 (A), D607.2 (A), D639.2 (A), D671.2 (A), D703.2 (A), D735.2 (A), D767.2 (A), D799.2 (A), D831.2 (A), D863.2 (A), D895.2 (A), D927.2 (A), D959.2 (A), D991.2 (A), D1023.2 (A), Q416.6 (C1)
/LED_control/LED_matrix/+31: D32.2 (A), D64.2 (A), D96.2 (A), D128.2 (A), D160.2 (A), D192.2 (A), D224.2 (A), D256.2 (A), D288.2 (A), D320.2 (A), D352.2 (A), D384.2 (A), D416.2 (A), D448.2 (A), D480.2 (A), D512.2 (A), D544.2 (A), D576.2 (A), D608.2 (A), D640.2 (A), D672.2 (A), D704.2 (A), D736.2 (A), D768.2 (A), D800.2 (A), D832.2 (A), D864.2 (A), D896.2 (A), D928.2 (A), D960.2 (A), D992.2 (A), D1024.2 (A), Q416.3 (C2)
/LED_control/LED_matrix/B0: D1.3 (BK), D2.3 (BK), D3.3 (BK), D4.3 (BK), D5.3 (BK), D6.3 (BK), D7.3 (BK), D8.3 (BK), D9.3 (BK), D10.3 (BK), D11.3 (BK), D12.3 (BK), D13.3 (BK), D14.3 (BK), D15.3 (BK), D16.3 (BK), D17.3 (BK), D18.3 (BK), D19.3 (BK), D20.3 (BK), D21.3 (BK), D22.3 (BK), D23.3 (BK), D24.3 (BK), D25.3 (BK), D26.3 (BK), D27.3 (BK), D28.3 (BK), D29.3 (BK), D30.3 (BK), D31.3 (BK), D32.3 (BK), R403.2
/LED_control/LED_matrix/B1: D33.3 (BK), D34.3 (BK), D35.3 (BK), D36.3 (BK), D37.3 (BK), D38.3 (BK), D39.3 (BK), D40.3 (BK), D41.3 (BK), D42.3 (BK), D43.3 (BK), D44.3 (BK), D45.3 (BK), D46.3 (BK), D47.3 (BK), D48.3 (BK), D49.3 (BK), D50.3 (BK), D51.3 (BK), D52.3 (BK), D53.3 (BK), D54.3 (BK), D55.3 (BK), D56.3 (BK), D57.3 (BK), D58.3 (BK), D59.3 (BK), D60.3 (BK), D61.3 (BK), D62.3 (BK), D63.3 (BK), D64.3 (BK), R406.2
/LED_control/LED_matrix/B2: D65.3 (BK), D66.3 (BK), D67.3 (BK), D68.3 (BK), D69.3 (BK), D70.3 (BK), D71.3 (BK), D72.3 (BK), D73.3 (BK), D74.3 (BK), D75.3 (BK), D76.3 (BK), D77.3 (BK), D78.3 (BK), D79.3 (BK), D80.3 (BK), D81.3 (BK), D82.3 (BK), D83.3 (BK), D84.3 (BK), D85.3 (BK), D86.3 (BK), D87.3 (BK), D88.3 (BK), D89.3 (BK), D90.3 (BK), D91.3 (BK), D92.3 (BK), D93.3 (BK), D94.3 (BK), D95.3 (BK), D96.3 (BK), R409.2
/LED_control/LED_matrix/B3: D97.3 (BK), D98.3 (BK), D99.3 (BK), D100.3 (BK), D101.3 (BK), D102.3 (BK), D103.3 (BK), D104.3 (BK), D105.3 (BK), D106.3 (BK), D107.3 (BK), D108.3 (BK), D109.3 (BK), D110.3 (BK), D111.3 (BK), D112.3 (BK), D113.3 (BK), D114.3 (BK), D115.3 (BK), D116.3 (BK), D117.3 (BK), D118.3 (BK), D119.3 (BK), D120.3 (BK), D121.3 (BK), D122.3 (BK), D123.3 (BK), D124.3 (BK), D125.3 (BK), D126.3 (BK), D127.3 (BK), D128.3 (BK), R412.2
/LED_control/LED_matrix/B4: D129.3 (BK), D130.3 (BK), D131.3 (BK), D132.3 (BK), D133.3 (BK), D134.3 (BK), D135.3 (BK), D136.3 (BK), D137.3 (BK), D138.3 (BK), D139.3 (BK), D140.3 (BK), D141.3 (BK), D142.3 (BK), D143.3 (BK), D144.3 (BK), D145.3 (BK), D146.3 (BK), D147.3 (BK), D148.3 (BK), D149.3 (BK), D150.3 (BK), D151.3 (BK), D152.3 (BK), D153.3 (BK), D154.3 (BK), D155.3 (BK), D156.3 (BK), D157.3 (BK), D158.3 (BK), D159.3 (BK), D160.3 (BK), R415.2
/LED_control/LED_matrix/B5: D161.3 (BK), D162.3 (BK), D163.3 (BK), D164.3 (BK), D165.3 (BK), D166.3 (BK), D167.3 (BK), D168.3 (BK), D169.3 (BK), D170.3 (BK), D171.3 (BK), D172.3 (BK), D173.3 (BK), D174.3 (BK), D175.3 (BK), D176.3 (BK), D177.3 (BK), D178.3 (BK), D179.3 (BK), D180.3 (BK), D181.3 (BK), D182.3 (BK), D183.3 (BK), D184.3 (BK), D185.3 (BK), D186.3 (BK), D187.3 (BK), D188.3 (BK), D189.3 (BK), D190.3 (BK), D191.3 (BK), D192.3 (BK), R418.2
/LED_control/LED_matrix/B6: D193.3 (BK), D194.3 (BK), D195.3 (BK), D196.3 (BK), D197.3 (BK), D198.3 (BK), D199.3 (BK), D200.3 (BK), D201.3 (BK), D202.3 (BK), D203.3 (BK), D204.3 (BK), D205.3 (BK), D206.3 (BK), D207.3 (BK), D208.3 (BK), D209.3 (BK), D210.3 (BK), D211.3 (BK), D212.3 (BK), D213.3 (BK), D214.3 (BK), D215.3 (BK), D216.3 (BK), D217.3 (BK), D218.3 (BK), D219.3 (BK), D220.3 (BK), D221.3 (BK), D222.3 (BK), D223.3 (BK), D224.3 (BK), R421.2
/LED_control/LED_matrix/B7: D225.3 (BK), D226.3 (BK), D227.3 (BK), D228.3 (BK), D229.3 (BK), D230.3 (BK), D231.3 (BK), D232.3 (BK), D233.3 (BK), D234.3 (BK), D235.3 (BK), D236.3 (BK), D237.3 (BK), D238.3 (BK), D239.3 (BK), D240.3 (BK), D241.3 (BK), D242.3 (BK), D243.3 (BK), D244.3 (BK), D245.3 (BK), D246.3 (BK), D247.3 (BK), D248.3 (BK), D249.3 (BK), D250.3 (BK), D251.3 (BK), D252.3 (BK), D253.3 (BK), D254.3 (BK), D255.3 (BK), D256.3 (BK), R424.2
/LED_control/LED_matrix/B8: D257.3 (BK), D258.3 (BK), D259.3 (BK), D260.3 (BK), D261.3 (BK), D262.3 (BK), D263.3 (BK), D264.3 (BK), D265.3 (BK), D266.3 (BK), D267.3 (BK), D268.3 (BK), D269.3 (BK), D270.3 (BK), D271.3 (BK), D272.3 (BK), D273.3 (BK), D274.3 (BK), D275.3 (BK), D276.3 (BK), D277.3 (BK), D278.3 (BK), D279.3 (BK), D280.3 (BK), D281.3 (BK), D282.3 (BK), D283.3 (BK), D284.3 (BK), D285.3 (BK), D286.3 (BK), D287.3 (BK), D288.3 (BK), R427.2
/LED_control/LED_matrix/B9: D289.3 (BK), D290.3 (BK), D291.3 (BK), D292.3 (BK), D293.3 (BK), D294.3 (BK), D295.3 (BK), D296.3 (BK), D297.3 (BK), D298.3 (BK), D299.3 (BK), D300.3 (BK), D301.3 (BK), D302.3 (BK), D303.3 (BK), D304.3 (BK), D305.3 (BK), D306.3 (BK), D307.3 (BK), D308.3 (BK), D309.3 (BK), D310.3 (BK), D311.3 (BK), D312.3 (BK), D313.3 (BK), D314.3 (BK), D315.3 (BK), D316.3 (BK), D317.3 (BK), D318.3 (BK), D319.3 (BK), D320.3 (BK), R430.2
/LED_control/LED_matrix/B10: D321.3 (BK), D322.3 (BK), D323.3 (BK), D324.3 (BK), D325.3 (BK), D326.3 (BK), D327.3 (BK), D328.3 (BK), D329.3 (BK), D330.3 (BK), D331.3 (BK), D332.3 (BK), D333.3 (BK), D334.3 (BK), D335.3 (BK), D336.3 (BK), D337.3 (BK), D338.3 (BK), D339.3 (BK), D340.3 (BK), D341.3 (BK), D342.3 (BK), D343.3 (BK), D344.3 (BK), D345.3 (BK), D346.3 (BK), D347.3 (BK), D348.3 (BK), D349.3 (BK), D350.3 (BK), D351.3 (BK), D352.3 (BK), R433.2
/LED_control/LED_matrix/B11: D353.3 (BK), D354.3 (BK), D355.3 (BK), D356.3 (BK), D357.3 (BK), D358.3 (BK), D359.3 (BK), D360.3 (BK), D361.3 (BK), D362.3 (BK), D363.3 (BK), D364.3 (BK), D365.3 (BK), D366.3 (BK), D367.3 (BK), D368.3 (BK), D369.3 (BK), D370.3 (BK), D371.3 (BK), D372.3 (BK), D373.3 (BK), D374.3 (BK), D375.3 (BK), D376.3 (BK), D377.3 (BK), D378.3 (BK), D379.3 (BK), D380.3 (BK), D381.3 (BK), D382.3 (BK), D383.3 (BK), D384.3 (BK), R436.2
/LED_control/LED_matrix/B12: D385.3 (BK), D386.3 (BK), D387.3 (BK), D388.3 (BK), D389.3 (BK), D390.3 (BK), D391.3 (BK), D392.3 (BK), D393.3 (BK), D394.3 (BK), D395.3 (BK), D396.3 (BK), D397.3 (BK), D398.3 (BK), D399.3 (BK), D400.3 (BK), D401.3 (BK), D402.3 (BK), D403.3 (BK), D404.3 (BK), D405.3 (BK), D406.3 (BK), D407.3 (BK), D408.3 (BK), D409.3 (BK), D410.3 (BK), D411.3 (BK), D412.3 (BK), D413.3 (BK), D414.3 (BK), D415.3 (BK), D416.3 (BK), R439.2
/LED_control/LED_matrix/B13: D417.3 (BK), D418.3 (BK), D419.3 (BK), D420.3 (BK), D421.3 (BK), D422.3 (BK), D423.3 (BK), D424.3 (BK), D425.3 (BK), D426.3 (BK), D427.3 (BK), D428.3 (BK), D429.3 (BK), D430.3 (BK), D431.3 (BK), D432.3 (BK), D433.3 (BK), D434.3 (BK), D435.3 (BK), D436.3 (BK), D437.3 (BK), D438.3 (BK), D439.3 (BK), D440.3 (BK), D441.3 (BK), D442.3 (BK), D443.3 (BK), D444.3 (BK), D445.3 (BK), D446.3 (BK), D447.3 (BK), D448.3 (BK), R442.2
/LED_control/LED_matrix/B14: D449.3 (BK), D450.3 (BK), D451.3 (BK), D452.3 (BK), D453.3 (BK), D454.3 (BK), D455.3 (BK), D456.3 (BK), D457.3 (BK), D458.3 (BK), D459.3 (BK), D460.3 (BK), D461.3 (BK), D462.3 (BK), D463.3 (BK), D464.3 (BK), D465.3 (BK), D466.3 (BK), D467.3 (BK), D468.3 (BK), D469.3 (BK), D470.3 (BK), D471.3 (BK), D472.3 (BK), D473.3 (BK), D474.3 (BK), D475.3 (BK), D476.3 (BK), D477.3 (BK), D478.3 (BK), D479.3 (BK), D480.3 (BK), R445.2
/LED_control/LED_matrix/B15: D481.3 (BK), D482.3 (BK), D483.3 (BK), D484.3 (BK), D485.3 (BK), D486.3 (BK), D487.3 (BK), D488.3 (BK), D489.3 (BK), D490.3 (BK), D491.3 (BK), D492.3 (BK), D493.3 (BK), D494.3 (BK), D495.3 (BK), D496.3 (BK), D497.3 (BK), D498.3 (BK), D499.3 (BK), D500.3 (BK), D501.3 (BK), D502.3 (BK), D503.3 (BK), D504.3 (BK), D505.3 (BK), D506.3 (BK), D507.3 (BK), D508.3 (BK), D509.3 (BK), D510.3 (BK), D511.3 (BK), D512.3 (BK), R448.2
/LED_control/LED_matrix/B16: D513.3 (BK), D514.3 (BK), D515.3 (BK), D516.3 (BK), D517.3 (BK), D518.3 (BK), D519.3 (BK), D520.3 (BK), D521.3 (BK), D522.3 (BK), D523.3 (BK), D524.3 (BK), D525.3 (BK), D526.3 (BK), D527.3 (BK), D528.3 (BK), D529.3 (BK), D530.3 (BK), D531.3 (BK), D532.3 (BK), D533.3 (BK), D534.3 (BK), D535.3 (BK), D536.3 (BK), D537.3 (BK), D538.3 (BK), D539.3 (BK), D540.3 (BK), D541.3 (BK), D542.3 (BK), D543.3 (BK), D544.3 (BK), R451.2
/LED_control/LED_matrix/B17: D545.3 (BK), D546.3 (BK), D547.3 (BK), D548.3 (BK), D549.3 (BK), D550.3 (BK), D551.3 (BK), D552.3 (BK), D553.3 (BK), D554.3 (BK), D555.3 (BK), D556.3 (BK), D557.3 (BK), D558.3 (BK), D559.3 (BK), D560.3 (BK), D561.3 (BK), D562.3 (BK), D563.3 (BK), D564.3 (BK), D565.3 (BK), D566.3 (BK), D567.3 (BK), D568.3 (BK), D569.3 (BK), D570.3 (BK), D571.3 (BK), D572.3 (BK), D573.3 (BK), D574.3 (BK), D575.3 (BK), D576.3 (BK), R454.2
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
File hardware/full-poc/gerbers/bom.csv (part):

Comment,Designator,Footprint,LCSC
100p,C612,Capacitor_SMD:C_0402_1005Metric,
2.7pF,C629,Capacitor_SMD:C_0402_1005Metric,
10n,"C602,C604,C606,C608,C614",Capacitor_SMD:C_0402_1005Metric,
"270nH, 500mΩ","L601,L602",Inductor_SMD:L_0805_2012Metric,
110p,"C618,C622,C625",Capacitor_SMD:C_0402_1005Metric,
ST25R3916B-AQWT,U601,Package_DFN_QFN:VQFN-32-1EP_5x5mm_P0.5mm_EP3.5x3.5mm_ThermalVias,
22p,"C616,C623",Capacitor_SMD:C_0402_1005Metric,
1u,"C301,C306,C307,C613",Capacitor_SMD:C_0402_1005Metric,
100n,"C101,C103,C104,C105,C106,C107,C108,C109,C110,C111,C112,C113,C201,C203,C204,C205,C206,C207,C208,C209,C210,C211,C212,C213,C609,C628",Capacitor_SMD:C_0402_1005Metric,
CMT2219A,U602,Package_DFN_QFN:QFN-16-1EP_3x3mm_P0.5mm_EP1.7x1.7mm_ThermalVias,
15p,"C117,C118,C217,C218,C610,C611",Capacitor_SMD:C_0402_1005Metric,
TAXM26M4RHBCCT2T,Y602,Crystal:Crystal_SMD_3225-4Pin_3.2x2.5mm,
LXRW0YV600-054,"VCC601,VCC602,VCC603",TFPC:LXRW0YV600-054,
10p,"C615,C619,C620,C624",Capacitor_SMD:C_0402_1005Metric,
3,"R601,R602",Resistor_SMD:R_0402_1005Metric,
680p,"C617,C621",Capacitor_SMD:C_0402_1005Metric,
2.2u,"C601,C603,C605,C607",Capacitor_SMD:C_0402_1005Metric,
25p,"C626,C627",Capacitor_SMD:C_0402_1005Metric,
BW868MNX1304,AE602,TFPC:BW868MNX1304,
3.9nH,L603,Inductor_SMD:L_0402_1005Metric,
6.8nH,L604,Inductor_SMD:L_0402_1005Metric,
5YMA27120091KF50EB,Y601,Crystal:Crystal_SMD_3225-4Pin_3.2x2.5mm,
NFC_TP2,TP602,TestPoint:TestPoint_Pad_D1.5mm,
NFC_TP1,TP601,TestPoint:TestPoint_Pad_D1.5mm,
Antenna_Loop,AE601,TFPC:NFC-Antenna,
10k,"R205,R208,R303,R307,R308,R309,R310",Resistor_SMD:R_0402_1005Metric,
BC857BS,"Q301,Q401,Q402,Q403,Q404,Q405,Q406,Q407,Q408,Q409,Q410,Q411,Q412,Q413,Q414,Q415,Q416",Package_TO_SOT_SMD:SOT-363_SC-70-6,
2u2,L301,Inductor_SMD:L_0603_1608Metric,
4.7u,"C102,C114,C115,C116,C202,C214,C215,C216,C305",Capacitor_SMD:C_0402_1005Metric,
47n,C304,Capacitor_SMD:C_0603_1608Metric,
H7650-33PR,U302,Package_TO_SOT_SMD:SOT-89-3,
10u,"C302,C303,C308",Capacitor_SMD:C_0402_1005Metric,
SI2302,Q302,PCM_JLCPCB:Q_SOT-23,
BAT_SOFT_OFF HY-DSIC02LS,SW301,Button_Switch_SMD:SW_DIP_SPSTx02_Slide_9.78x7.26mm_W8.61mm_P2.54mm,
1.5k,R306,Resistor_SMD:R_0402_1005Metric,
5.1k,"R301,R302,R304",Resistor_SMD:R_0402_1005Metric,
220,R305,Resistor_SMD:R_0402_1005Metric,
Battery_Cell,BT301,TFPC:BH-18650-B6AA002,
"Connector, USB-TYPE-C-16P","J202,J301",PCM_JLCPCB:TYPE-C-SMD_HX-TYPE-C-16PIN,C2927039
BQ24195LRGER,U301,Package_DFN_QFN:VQFN-24-1EP_4x4mm_P0.5mm_EP2.45x2.45mm_ThermalVias,
82,"R403,R406,R409,R412,R415,R418,R421,R424,R427,R430,R433,R436,R439,R442,R445,R448,R451,R454,R457,R460,R463,R466,R469,R472,R475,R478,R481,R484,R487,R490,R493,R496",Resistor_SMD:R_0402_1005Metric,
130,"R401,R404,R407,R410,R413,R416,R419,R422,R425,R428,R431,R434,R437,R440,R443,R446,R449,R452,R455,R458,R461,R464,R467,R470,R473,R476,R479,R482,R485,R488,R491,R494",Resistor_SMD:R_0402_1005Metric,
360,"R402,R405,R408,R411,R414,R417,R420,R423,R426,R429,R432,R435,R438,R441,R444,R447,R450,R453,R456,R459,R462,R465,R468,R471,R474,R477,R480,R483,R486,R489,R492,R495",Resistor_SMD:R_0402_1005Metric,
74HC138LQ/TR,"U413,U414,U415,U416,U417,U418",Package_DFN_QFN:QFN-16-1EP_3x3mm_P0.5mm_EP1.7x1.7mm_ThermalVias,
1k,"R104,R105,R106,R107,R204,R206,R207,R497,R498,R499,R500,R501,R502,R503,R504,R505,R506,R507,R508,R509,R510,R511,R512,R513,R514,R515,R516,R517,R518,R519,R520,R521,R522,R523,R524,R525,R526,R527,R528",Resistor_SMD:R_0402_1005Metric,
74HC595BQ,"U401,U402,U403,U404,U405,U406,U407,U408,U409,U410,U411,U412",Package_DFN_QFN:DHVQFN-16-1EP_2.5x3.5mm_P0.5mm_EP1x2mm,
100u,"C401,C402,C403,C404,C405,C406,C407,C408,C409",Capacitor_SMD:CP_Elec_5x5.4,
LED_RABG,"D1,D2,D3,D4,D5,D6,D7,D8,D9,D10,D11,D12,D13,D14,D15,D16,D17,D18,D19,D20,D21,D22,D23,D24,D25,D26,D27,D28,D29,D30,D31,D32,D33,D34,D35,D36,D37,D38,D39,D40,D41,D42,D43,D44,D45,D46,D47,D48,D49,D50,D51,D52,D53,D54,D55,D56,D57,D58,D59,D60,D61,D62,D63,D64,D65,D66,D67,D68,D69,D70,D71,D72,D73,D74,D75,D76,D77,D78,D79,D80,D81,D82,D83,D84,D85,D86,D87,D88,D89,D90,D91,D92,D93,D94,D95,D96,D97,D98,D99,D100",,
LED_RABG,"D101,D102,D103,D104,D105,D106,D107,D108,D109,D110,D111,D112,D113,D114,D115,D116,D117,D118,D119,D120,D121,D122,D123,D124,D125,D126,D127,D128,D129,D130,D131,D132,D133,D134,D135,D136,D137,D138,D139,D140,D141,D142,D143,D144,D145,D146,D147,D148,D149,D150,D151,D152,D153,D154,D155,D156,D157,D158,D159,D160,D161,D162,D163,D164,D165,D166,D167,D168,D169,D170,D171,D172,D173,D174,D175,D176,D177,D178,D179,D180,D181,D182,D183,D184,D185,D186,D187,D188,D189,D190,D191,D192,D193,D194,D195,D196,D197,D198,D199,D200",,
LED_RABG,"D201,D202,D203,D204,D205,D206,D207,D208,D209,D210,D211,D212,D213,D214,D215,D216,D217,D218,D219,D220,D221,D222,D223,D224,D225,D226,D227,D228,D229,D230,D231,D232,D233,D234,D235,D236,D237,D238,D239,D240,D241,D242,D243,D244,D245,D246,D247,D248,D249,D250,D251,D252,D253,D254,D255,D256,D257,D258,D259,D260,D261,D262,D263,D264,D265,D266,D267,D268,D269,D270,D271,D272,D273,D274,D275,D276,D277,D278,D279,D280,D281,D282,D283,D284,D285,D286,D287,D288,D289,D290,D291,D292,D293,D294,D295,D296,D297,D298,D299,D300",,
LED_RABG,"D301,D302,D303,D304,D305,D306,D307,D308,D309,D310,D311,D312,D313,D314,D315,D316,D317,D318,D319,D320,D321,D322,D323,D324,D325,D326,D327,D328,D329,D330,D331,D332,D333,D334,D335,D336,D337,D338,D339,D340,D341,D342,D343,D344,D345,D346,D347,D348,D349,D350,D351,D352,D353,D354,D355,D356,D357,D358,D359,D360,D361,D362,D363,D364,D365,D366,D367,D368,D369,D370,D371,D372,D373,D374,D375,D376,D377,D378,D379,D380,D381,D382,D383,D384,D385,D386,D387,D388,D389,D390,D391,D392,D393,D394,D395,D396,D397,D398,D399,D400",,
LED_RABG,"D401,D402,D403,D404,D405,D406,D407,D408,D409,D410,D411,D412,D413,D414,D415,D416,D417,D418,D419,D420,D421,D422,D423,D424,D425,D426,D427,D428,D429,D430,D431,D432,D433,D434,D435,D436,D437,D438,D439,D440,D441,D442,D443,D444,D445,D446,D447,D448,D449,D450,D451,D452,D453,D454,D455,D456,D457,D458,D459,D460,D461,D462,D463,D464,D465,D466,D467,D468,D469,D470,D471,D472,D473,D474,D475,D476,D477,D478,D479,D480,D481,D482,D483,D484,D485,D486,D487,D488,D489,D490,D491,D492,D493,D494,D495,D496,D497,D498,D499,D500",,
LED_RABG,"D501,D502,D503,D504,D505,D506,D507,D508,D509,D510,D511,D512,D513,D514,D515,D516,D517,D518,D519,D520,D521,D522,D523,D524,D525,D526,D527,D528,D529,D530,D531,D532,D533,D534,D535,D536,D537,D538,D539,D540,D541,D542,D543,D544,D545,D546,D547,D548,D549,D550,D551,D552,D553,D554,D555,D556,D557,D558,D559,D560,D561,D562,D563,D564,D565,D566,D567,D568,D569,D570,D571,D572,D573,D574,D575,D576,D577,D578,D579,D580,D581,D582,D583,D584,D585,D586,D587,D588,D589,D590,D591,D592,D593,D594,D595,D596,D597,D598,D599,D600",,
LED_RABG,"D601,D602,D603,D604,D605,D606,D607,D608,D609,D610,D611,D612,D613,D614,D615,D616,D617,D618,D619,D620,D621,D622,D623,D624,D625,D626,D627,D628,D629,D630,D631,D632,D633,D634,D635,D636,D637,D638,D639,D640,D641,D642,D643,D644,D645,D646,D647,D648,D649,D650,D651,D652,D653,D654,D655,D656,D657,D658,D659,D660,D661,D662,D663,D664,D665,D666,D667,D668,D669,D670,D671,D672,D673,D674,D675,D676,D677,D678,D679,D680,D681,D682,D683,D684,D685,D686,D687,D688,D689,D690,D691,D692,D693,D694,D695,D696,D697,D698,D699,D700",,
LED_RABG,"D701,D702,D703,D704,D705,D706,D707,D708,D709,D710,D711,D712,D713,D714,D715,D716,D717,D718,D719,D720,D721,D722,D723,D724,D725,D726,D727,D728,D729,D730,D731,D732,D733,D734,D735,D736,D737,D738,D739,D740,D741,D742,D743,D744,D745,D746,D747,D748,D749,D750,D751,D752,D753,D754,D755,D756,D757,D758,D759,D760,D761,D762,D763,D764,D765,D766,D767,D768,D769,D770,D771,D772,D773,D774,D775,D776,D777,D778,D779,D780,D781,D782,D783,D784,D785,D786,D787,D788,D789,D790,D791,D792,D793,D794,D795,D796,D797,D798,D799,D800",,
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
